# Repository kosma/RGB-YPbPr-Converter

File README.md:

# RGB-YPbPr-Converter
RGB-YPbPr Converter using opamps.

Based on [LT6550 reference design](https://www.analog.com/en/products/lt6550.html)

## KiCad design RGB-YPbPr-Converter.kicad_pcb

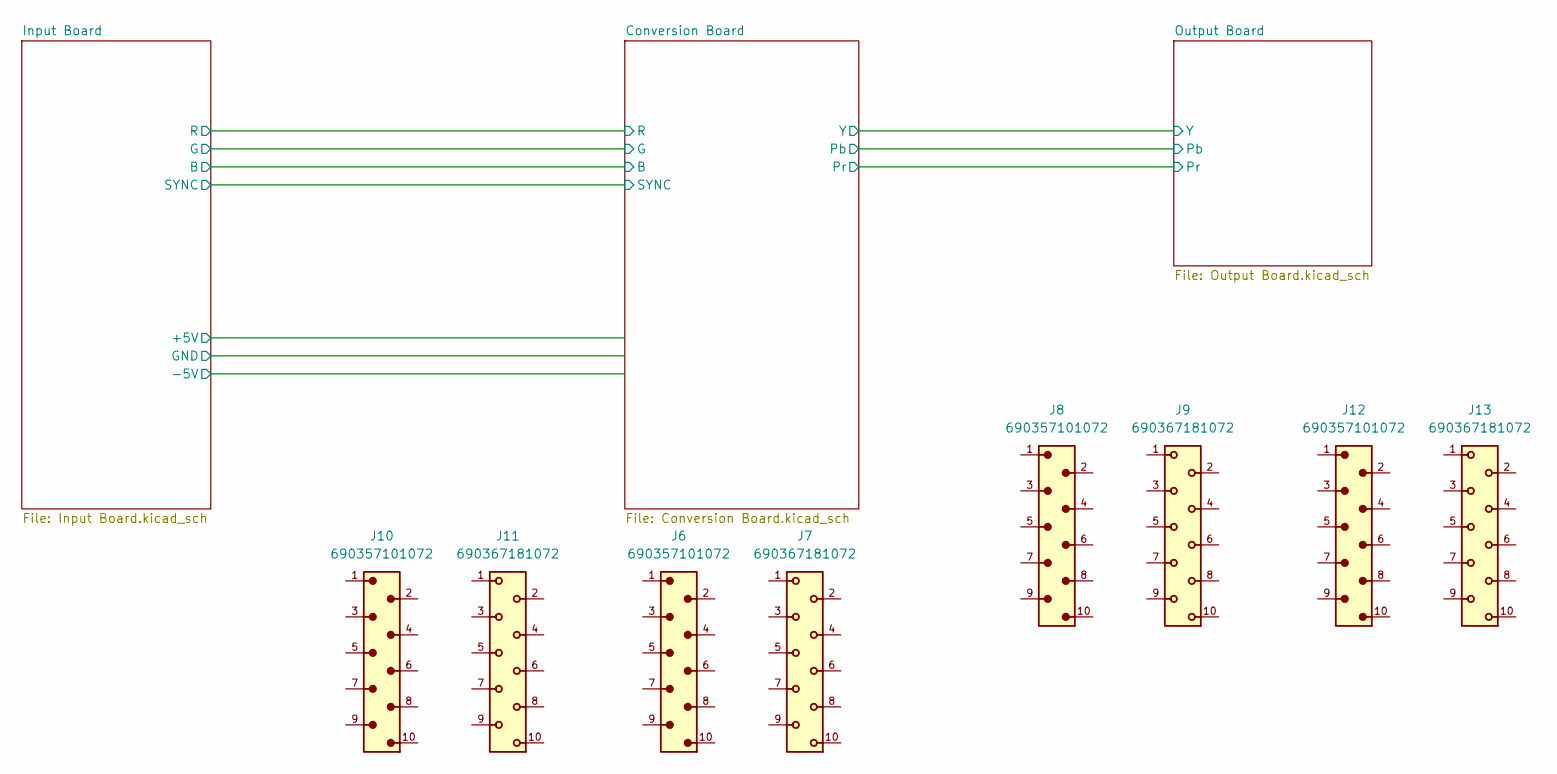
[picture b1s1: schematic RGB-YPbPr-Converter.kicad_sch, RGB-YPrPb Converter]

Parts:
J6, J8, J10, J12: 690357101072; PART-NUMBER 690357101072
J7, J9, J11, J13: 690367181072; PART-NUMBER 690367181072

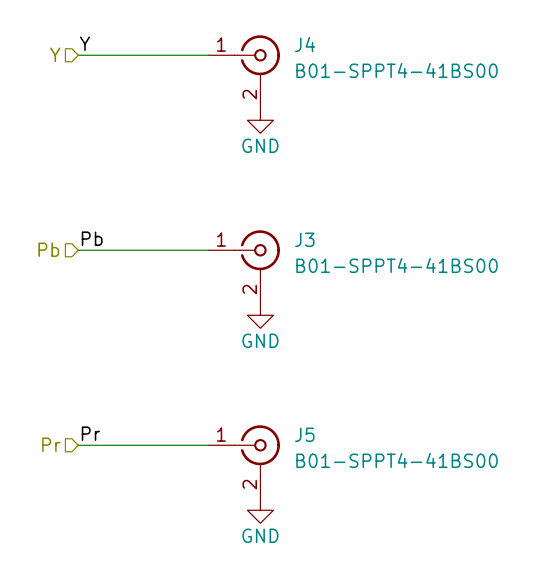
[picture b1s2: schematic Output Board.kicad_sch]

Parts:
J3, J4, J5: B01-SPPT4-41BS00; Part Number B01-SPPT4-41BS00

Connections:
/Conversion Board/Pb: J3.1 (In); also elsewhere on the board
/Conversion Board/Pr: J5.1 (In); also elsewhere on the board
/Conversion Board/Y: J4.1 (In); also elsewhere on the board
GND: J3.2 (Ext), J4.2 (Ext), J5.2 (Ext); also elsewhere on the board

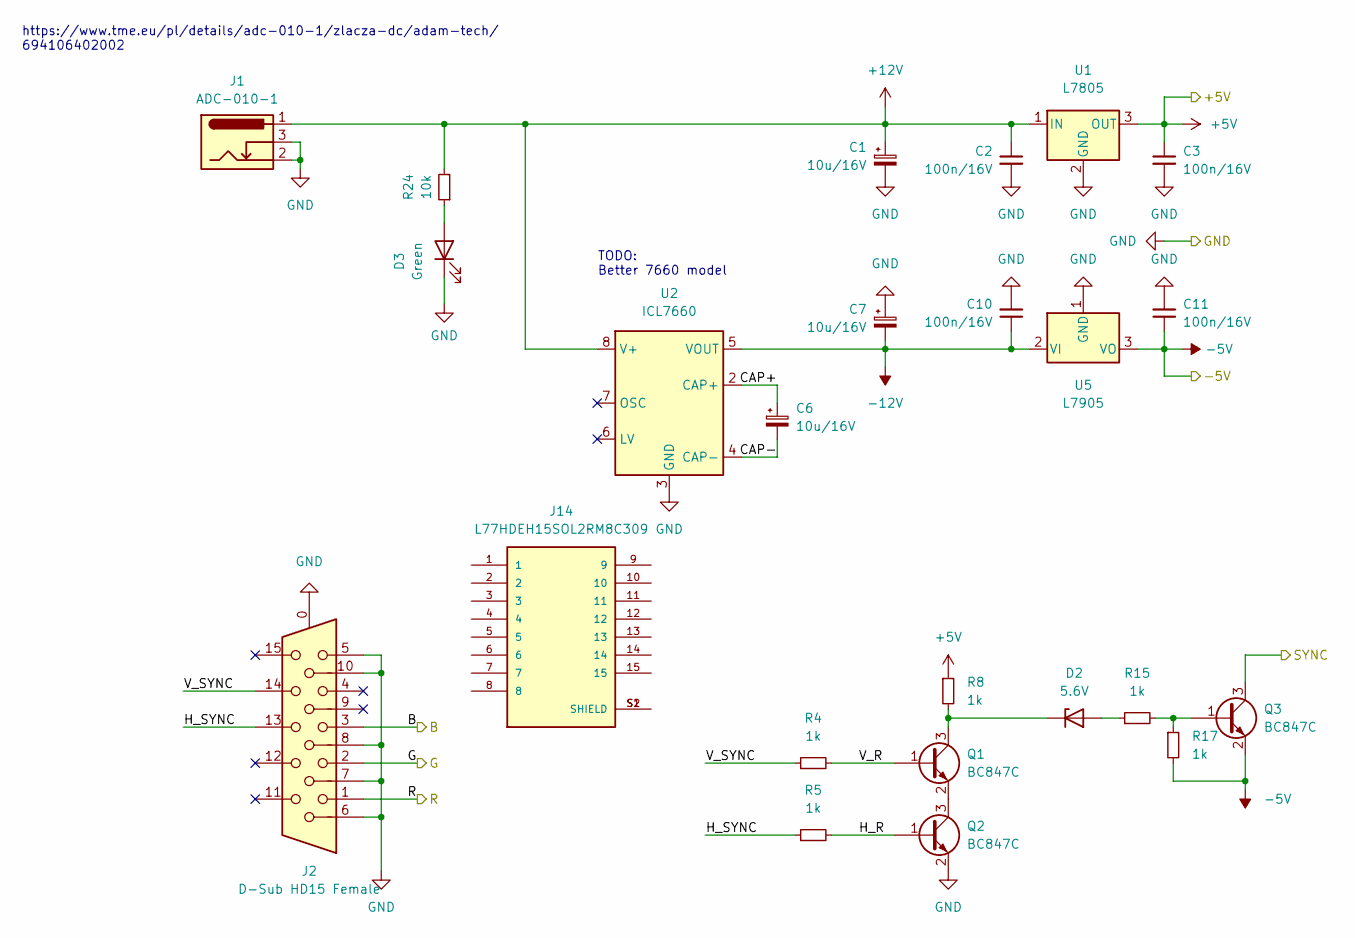
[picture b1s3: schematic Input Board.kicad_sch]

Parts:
C1, C6, C7: 10u/16V; C_1206_3216Metric; Part Number 10u/16V
C2, C3, C10, C11: 100n/16V; C_0603_1608Metric; Part Number 100n/16V
D2: 5.6V; D_SOD-323_HandSoldering; Part Number BZX384-C5V6,115
D3: Green; LED_0805_2012Metric; Part Number LED 0805 Green
J1: ADC-010-1; Part Number ADC-010-1
J2: D-Sub HD15 Female; DSUB-15-HD_Female_Vertical_P2.29x1.98mm_MountingHoles
J14: L77HDEH15SOL2RM8C309; AMPHENOL_L77HDEH15SOL2RM8C309; PARTREV 1
Q1, Q2, Q3: BC847C; SOT-23; Part Number BC847C
R4, R5, R8, R15, R17: 1k; R_0603_1608Metric
R24: 10k; R_0603_1608Metric
U1: L7805; SOT-89-3
U2: ICL7660; SOIC-8_3.9x4.9mm_P1.27mm; Part Number ICL7660AIBAZA; Mouser 968-ICL7660AIBAZA
U5: L7905; SOT-89-3

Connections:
+5V: C3.1, R8.1, U1.3 (OUT); also elsewhere on the board
+12V: C1.1, C2.1, J1.1, R24.2, U1.1 (IN), U2.8 (V+)
-5V: C11.1, Q3.2 (E), R17.2, U5.3 (VO); also elsewhere on the board
-12V: C7.2, C10.1, U2.5 (VOUT), U5.2 (VI)
/Conversion Board/B: J2.3; also elsewhere on the board
/Conversion Board/G: J2.2; also elsewhere on the board
/Conversion Board/R: J2.1; also elsewhere on the board
/Conversion Board/SYNC: Q3.3 (C); also elsewhere on the board
/Input Board/CAP+: C6.1, U2.2 (CAP+)
/Input Board/CAP-: C6.2, U2.4 (CAP-)
/Input Board/H_R: Q2.1 (B), R5.2
/Input Board/H_SYNC: J2.13, R5.1
/Input Board/V_R: Q1.1 (B), R4.2
/Input Board/V_SYNC: J2.14, R4.1
GND: C1.2, C2.2, C3.2, C7.1, C10.2, C11.2, D3.1 (K), J1.2, J1.3, J2.0, J2.5, J2.6, J2.7, J2.8, J2.10, Q2.2 (E), U1.2 (GND), U2.3 (GND), U5.1 (GND); also elsewhere on the board
unnamed: D2.1 (K), Q1.3 (C), R8.2
unnamed: D2.2 (A), R15.1
unnamed: D3.2 (A), R24.1
unnamed: J14.S1 (SHIELD), J14.S2 (SHIELD)
unnamed: Q1.2 (E), Q2.3 (C)
unnamed: Q3.1 (B), R15.2, R17.1

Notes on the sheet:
https://www.tme.eu/pl/details/adc-010-1/zlacza-dc/adam-tech/ 694106402002
TODO: Better 7660 model

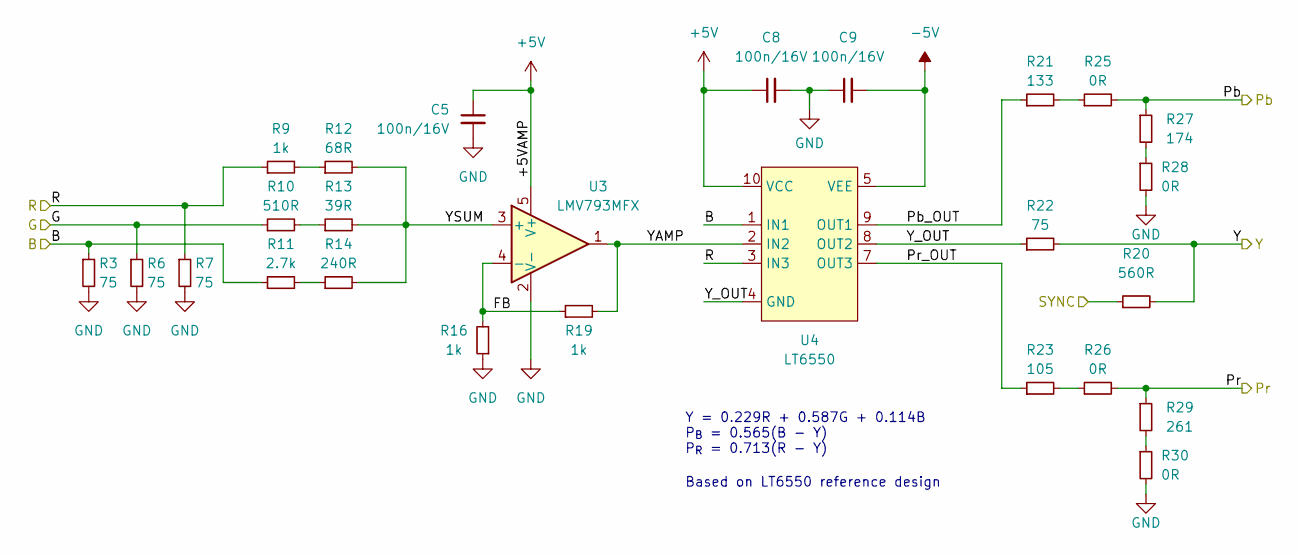
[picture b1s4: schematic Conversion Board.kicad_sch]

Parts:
C5, C8, C9: 100n/16V; C_0603_1608Metric; Part Number 100n/16V
R3, R6, R7, R22: 75; R_0603_1608Metric
R9, R16, R19: 1k; R_0603_1608Metric
R10: 510R; R_0603_1608Metric
R11: 2.7k; R_0603_1608Metric
R12: 68R; R_0603_1608Metric
R13: 39R; R_0603_1608Metric
R14: 240R; R_0603_1608Metric
R20: 560R; R_0603_1608Metric
R21: 133; R_0603_1608Metric
R23: 105; R_0603_1608Metric
R25, R26, R28, R30: 0R; R_0603_1608Metric
R27: 174; R_0603_1608Metric
R29: 261; R_0603_1608Metric
U3: LMV793MFX; SOT-23-5; Part Number LMV793MFX/NOPB; Mouser 926-LMV793MFX/NOPB
U4: LT6550; MSOP-10_3x3mm_P0.5mm; Part Number LT6550CMS#PBF; Mouser LT6550CMS#PBF

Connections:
+5V: C5.1, C8.1, U3.5 (V+), U4.10 (VCC); also elsewhere on the board
-5V: C9.2, U4.5 (VEE); also elsewhere on the board
/Conversion Board/B: R3.1, R11.1, U4.1 (IN1); also elsewhere on the board
/Conversion Board/FB: R16.2, R19.1, U3.4 (-)
/Conversion Board/G: R6.1, R10.1; also elsewhere on the board
/Conversion Board/Pb: R25.2, R27.1; also elsewhere on the board
/Conversion Board/Pb_OUT: R21.1, U4.9 (OUT1)
/Conversion Board/Pr: R26.2, R29.1; also elsewhere on the board
/Conversion Board/Pr_OUT: R23.1, U4.7 (OUT3)
/Conversion Board/R: R7.1, R9.1, U4.3 (IN3); also elsewhere on the board
/Conversion Board/SYNC: R20.1; also elsewhere on the board
/Conversion Board/Y: R20.2, R22.2; also elsewhere on the board
/Conversion Board/YAMP: R19.2, U3.1, U4.2 (IN2)
/Conversion Board/YSUM: R12.2, R13.2, R14.2, U3.3 (+)
/Conversion Board/Y_OUT: R22.1, U4.4 (GND), U4.8 (OUT2)
GND: C5.2, C8.2, C9.1, R3.2, R6.2, R7.2, R16.1, R28.2, R30.2, U3.2 (V-); also elsewhere on the board
unnamed: R10.2, R13.1
unnamed: R11.2, R14.1
unnamed: R9.2, R12.1
unnamed: R21.2, R25.1
unnamed: R23.2, R26.1
unnamed: R27.2, R28.1
unnamed: R29.2, R30.1

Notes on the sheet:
Based on LT6550 reference design
Y = 0.229R + 0.587G + 0.114B P_{B} = 0.565(B - Y) P_{R} = 0.713(R - Y)

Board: 2 copper layers, 66 parts (9 on the bottom side), 37 nets, no tracks yet.

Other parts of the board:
kibuzzard-633F4DF1: G***; kibuzzard-633F4DF1
kibuzzard-63377B96: G***; kibuzzard-63377B96
kibuzzard-6396650B: G***; kibuzzard-6396650B
kibuzzard-6396651D: G***; kibuzzard-6396651D
kibuzzard-63966514: G***; kibuzzard-63966514

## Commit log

2022-10-05 Add H and V sync pulses to Y channel
2022-10-06 finished board
2022-10-07 fixes
2022-10-07 generate project outputs
2022-12-08 .gitignore: add Mac cruft
2022-12-08 WIP of sandwich version
2022-12-12 add more 3D models
2023-06-11 emergency version for decrunch 2023
2023-06-23 gerbers + resistor values
